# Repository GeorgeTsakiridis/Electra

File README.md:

Electra is a WIP DRSSTC Tesla Coil, aimed to have a power rating of about 7-8 kW.

<h1>Project Structure:</h1>
<ul>
   <li>DRSSTC MIDI Interrupter: The original Interrupter Controller.</li>
   <li>DRSSTC MIDI Interrupter 2: The new Interrupter Controller.</li>
   <li>Model: A 3D Model of the Tesla Coil.</li>
</ul>

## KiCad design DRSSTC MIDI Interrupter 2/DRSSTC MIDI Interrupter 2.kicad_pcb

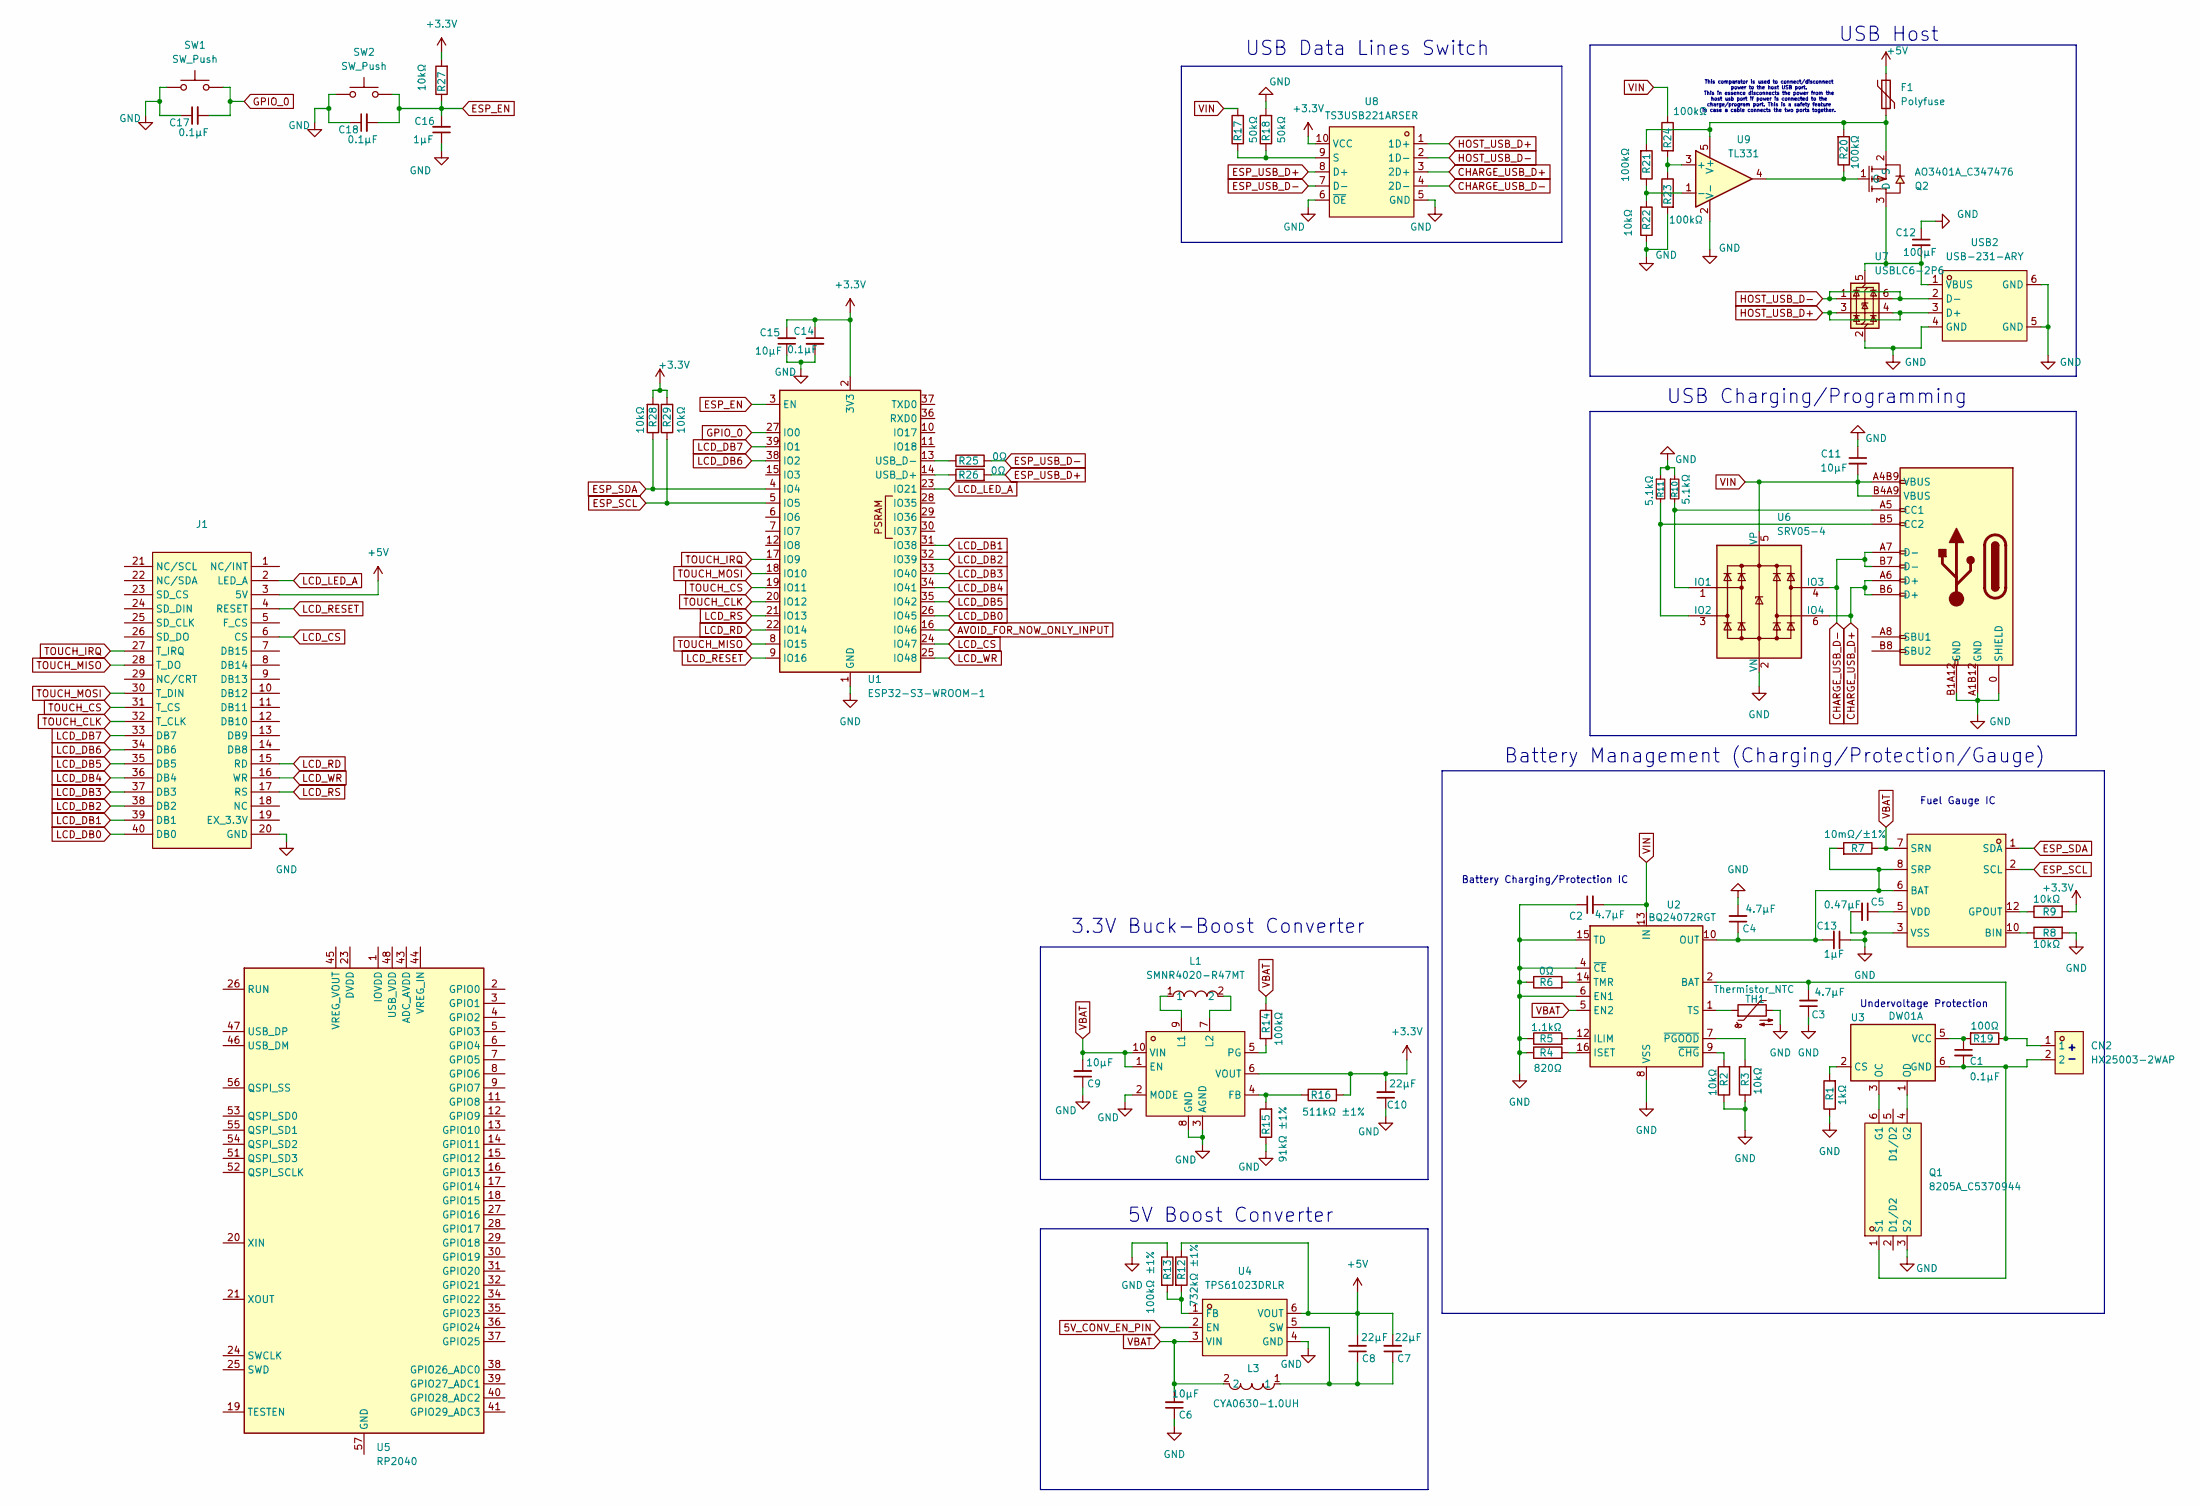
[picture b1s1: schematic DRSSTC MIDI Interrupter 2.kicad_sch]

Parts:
C1, C14, C17, C18: 0.1μF; C_0805_2012Metric_Pad1.18x1.45mm_HandSolder
C2, C3, C4: 4.7μF; C_0805_2012Metric_Pad1.18x1.45mm_HandSolder
C5: 0.47μF; C_0805_2012Metric_Pad1.18x1.45mm_HandSolder
C6, C9, C11, C15: 10μF; C_0805_2012Metric_Pad1.18x1.45mm_HandSolder
C7, C8, C10: 22μF; C_0805_2012Metric_Pad1.18x1.45mm_HandSolder
C12: 100μF; C_0805_2012Metric_Pad1.18x1.45mm_HandSolder
C13, C16: 1μF; C_0805_2012Metric_Pad1.18x1.45mm_HandSolder
CN2: HX25003-2WAP; CONN-TH_2P-P2.50_HX25003-2WAP; LCSC Part C442326
F1: Polyfuse; R_0805_2012Metric_Pad1.20x1.40mm_HandSolder; LCSC ID C2843994
J1: LCD
L1: SMNR4020-R47MT; IND-SMD_L4.0-W4.0_SMNR4020; LCSC Part C467058
L3: CYA0630-1.0UH; IND-SMD_L7.2-W6.6_GPSR0730; LCSC Part C5189744
Q1: 8205A_C5370944; SOT-23-6_L2.9-W1.6-P0.95-LS2.8-BR; LCSC Part C5370944
Q2: AO3401A_C347476; SOT-23_L2.9-W1.3-P1.90-LS2.4-BR; LCSC Part C347476
R1: 1kΩ; R_0805_2012Metric_Pad1.20x1.40mm_HandSolder
R2, R3, R8, R9, R22, R27, R28, R29: 10kΩ; R_0805_2012Metric_Pad1.20x1.40mm_HandSolder
R4: 820Ω; R_0805_2012Metric_Pad1.20x1.40mm_HandSolder
R5: 1.1kΩ; R_0805_2012Metric_Pad1.20x1.40mm_HandSolder
R6, R25, R26: 0Ω; R_0805_2012Metric_Pad1.20x1.40mm_HandSolder
R7: 10mΩ/±1%; R_1206_3216Metric_Pad1.30x1.75mm_HandSolder
R10, R11: 5.1kΩ; R_0805_2012Metric
R12: 732kΩ ±1%; R_0805_2012Metric_Pad1.20x1.40mm_HandSolder
R13: 100kΩ ±1%; R_0805_2012Metric_Pad1.20x1.40mm_HandSolder
R14, R20, R21, R23, R24: 100kΩ; R_0805_2012Metric_Pad1.20x1.40mm_HandSolder
R15: 91kΩ ±1%; R_0805_2012Metric_Pad1.20x1.40mm_HandSolder
R16: 511kΩ ±1%; R_0805_2012Metric_Pad1.20x1.40mm_HandSolder
R17, R18: 50kΩ; R_0805_2012Metric_Pad1.20x1.40mm_HandSolder
R19: 100Ω; R_0805_2012Metric_Pad1.20x1.40mm_HandSolder
SW1, SW2: SW_Push
TH1: Thermistor_NTC
U1: ESP32-S3-WROOM-1
U2: BQ24072RGT; VQFN-16-1EP_3x3mm_P0.5mm_EP1.6x1.6mm
U3: DW01A; SOT-23-6
U4: TPS61023DRLR; SOT-563_L1.6-W1.2-P0.50-LS1.6-BR; LCSC Part C919459
U5: RP2040; QFN-56-1EP_7x7mm_P0.4mm_EP3.2x3.2mm
U6: SRV05-4; SOT-23-6_L2.9-W1.6-P0.95-LS2.8-BR
U7: USBLC6-2P6; SOT-666
U8: TS3USB221ARSER; UQFN-10_L2.0-W1.5-P0.50-BL; LCSC Part C128396
U9: TL331; SOT-23-5; LCSC Part Number C80942
U10: TPS63802DLAR; VSON-10_L3.0-W2.0-P0.50-TL; LCSC Part C2845237
U11: BQ27441DRZR-G1B; SON-12_L4.0-W2.5-P0.40-BL-EP; LCSC Part C473374
USB1: HH 16P-CB TYPE-C (Y007); USB-C-SMD_HH-16P-CB-TYPE-C-Y007; LCSC Part C52711231
USB2: USB-231-ARY; USB-A-TH_USB-231-ARY; LCSC Part C720525

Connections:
5V_CONV_EN_PIN: U4.2 (EN)
+3.3V: C10.2, C14.1, C15.2, R9.2, R16.2, R27.2, R28.2, R29.2, U1.2 (3V3), U8.10 (VCC), U10.6 (VOUT)
+5V: C7.2, C8.2, F1.1, J1.3 (5V), R12.1, U4.6 (VOUT)
AVOID_FOR_NOW_ONLY_INPUT: U1.16 (IO46)
CHARGE_USB_D+: U6.6 (IO4), U8.3 (2D+), USB1.A6 (D+), USB1.B6 (D+)
CHARGE_USB_D-: U6.4 (IO3), U8.4 (2D-), USB1.A7 (D-), USB1.B7 (D-)
ESP_EN: C16.2, C18.2, R27.1, SW2.2, U1.3 (EN)
ESP_SCL: R29.1, U1.5 (IO5), U11.2 (SCL)
ESP_SDA: R28.1, U1.4 (IO4), U11.1 (SDA)
ESP_USB_D+: R26.2, U8.8 (D+)
ESP_USB_D-: R25.2, U8.7 (D-)
GND: C2.1, C3.1, C4.2, C5.2, C6.1, C9.1, C10.1, C11.1, C12.1, C13.1, C14.2, C15.1, C16.1, C17.1, C18.1, J1.20 (GND), Q1.3 (S2), R1.1, R2.1, R3.1, R4.1, R5.1, R6.1, R8.2, R10.1, R11.1, R13.1, R15.1, R18.2, R22.1, R23.2, SW1.1, SW2.1, TH1.2, U1.1 (GND), U1.40 (GND), U1.41 (GND), U2.4 (~CE), U2.6 (EN1), U2.8 (VSS), U2.15 (TD), U2.17 (VSS), U4.4 (GND), U6.2 (VN), U7.2 (GND), U8.5 (GND), U8.6 (~OE), U9.2 (V-), U10.2 (MODE), U10.3 (AGND), U10.8 (GND), U11.3 (VSS), USB1.0 (SHIELD), USB1.A1B12 (GND), USB1.B1A12 (GND), USB2.4 (GND), USB2.5 (GND), USB2.6 (GND)
GPIO_0: C17.2, SW1.2, U1.27 (IO0)
HOST_USB_D+: U7.3 (I/O2), U7.4 (I/O2), U8.1 (1D+), USB2.3 (D+)
HOST_USB_D-: U7.1 (I/O1), U7.6 (I/O1), U8.2 (1D-), USB2.2 (D-)
LCD_CS: J1.6 (CS), U1.24 (IO47)
LCD_DB0: J1.40 (DB0), U1.26 (IO45)
LCD_DB1: J1.39 (DB1), U1.31 (IO38)
LCD_DB2: J1.38 (DB2), U1.32 (IO39)
LCD_DB3: J1.37 (DB3), U1.33 (IO40)
LCD_DB4: J1.36 (DB4), U1.34 (IO41)
LCD_DB5: J1.35 (DB5), U1.35 (IO42)
LCD_DB6: J1.34 (DB6), U1.38 (IO2)
LCD_DB7: J1.33 (DB7), U1.39 (IO1)
LCD_LED_A: J1.2 (LED_A), U1.23 (IO21)
LCD_RD: J1.15 (RD), U1.22 (IO14)
LCD_RESET: J1.4 (RESET), U1.9 (IO16)
LCD_RS: J1.17 (RS), U1.21 (IO13)
LCD_WR: J1.16 (WR), U1.25 (IO48)
unnamed: C3.2, CN2.1, R19.1, U2.2 (BAT), U2.3 (BAT)
unnamed: Q1.6 (G1), U3.3 (OC)
unnamed: Q1.4 (G2), U3.1 (OD)
unnamed: C1.2, CN2.2, Q1.1 (S1), U3.6 (GND)
unnamed: C12.2, Q2.3 (D), U7.5 (VBUS), USB2.1 (VBUS)
unnamed: Q2.1 (G), R20.1, U9.4
unnamed: F1.2, Q2.2 (S), R20.2, R21.2, U9.5 (V+)
unnamed: R26.1, U1.14 (USB_D+)
unnamed: R25.1, U1.13 (USB_D-)
unnamed: R5.2, U2.12 (ILIM)
unnamed: R4.2, U2.16 (ISET)
unnamed: R6.2, U2.14 (TMR)
unnamed: TH1.1, U2.1 (TS)
unnamed: R2.2, U2.9 (~CHG)
unnamed: R3.2, U2.7 (~PGOOD)
unnamed: R1.2, U3.2 (CS)
unnamed: C1.1, R19.2, U3.5 (VCC)
unnamed: R12.2, R13.2, U4.1 (FB)
unnamed: C7.1, C8.1, L3.1, U4.5 (SW)
unnamed: U5.23 (DVDD), U5.50 (DVDD)
unnamed: U5.1 (IOVDD), U5.10 (IOVDD), U5.22 (IOVDD), U5.33 (IOVDD), U5.42 (IOVDD), U5.49 (IOVDD)
unnamed: R10.2, U6.1 (IO1), USB1.A5 (CC1)
unnamed: R11.2, U6.3 (IO2), USB1.B5 (CC2)
unnamed: R17.1, R18.1, U8.9 (S)
unnamed: R23.1, R24.2, U9.3 (+)
unnamed: R21.1, R22.2, U9.1 (-)
unnamed: R15.2, R16.1, U10.4 (FB)
unnamed: L1.1, U10.9 (L1)
unnamed: L1.2, U10.7 (L2)
unnamed: R14.2, U10.5 (PG)
unnamed: C4.1, C13.2, R7.2, U2.10 (OUT), U2.11 (OUT), U11.6 (BAT), U11.8 (SRP)
unnamed: R8.1, U11.10 (BIN)
unnamed: R9.1, U11.12 (GPOUT)
unnamed: C5.1, U11.5 (VDD)
TOUCH_CLK: J1.32 (T_CLK), U1.20 (IO12)
TOUCH_CS: J1.31 (T_CS), U1.19 (IO11)
TOUCH_IRQ: J1.27 (T_IRQ), U1.17 (IO9)
TOUCH_MISO: J1.28 (T_DO), U1.8 (IO15)
TOUCH_MOSI: J1.30 (T_DIN), U1.18 (IO10)
VBAT: C6.2, C9.2, L3.2, R7.1, R14.1, U2.5 (EN2), U4.3 (VIN), U10.1 (EN), U10.10 (VIN), U11.7 (SRN)
VIN: C2.2, C11.2, R17.2, R24.1, U2.13 (IN), U6.5 (VP), USB1.A4B9 (VBUS), USB1.B4A9 (VBUS)

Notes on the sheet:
Battery Management (Charging/Protection/Gauge)
+ -
5V Boost Converter
This comparator is used to connect/disconnect power to the host USB port. This in essence disconnects the power from the host usb port if power is connected to the charge/program port. This is a safety feature in case a cable connects the two ports together.
3.3V Buck-Boost Converter
Fuel Gauge IC
USB Data Lines Switch
USB Host
USB Charging/Programming
Battery Charging/Protection IC
Undervoltage Protection

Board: 2 copper layers, 67 parts (0 on the bottom side), 67 nets, no tracks yet.

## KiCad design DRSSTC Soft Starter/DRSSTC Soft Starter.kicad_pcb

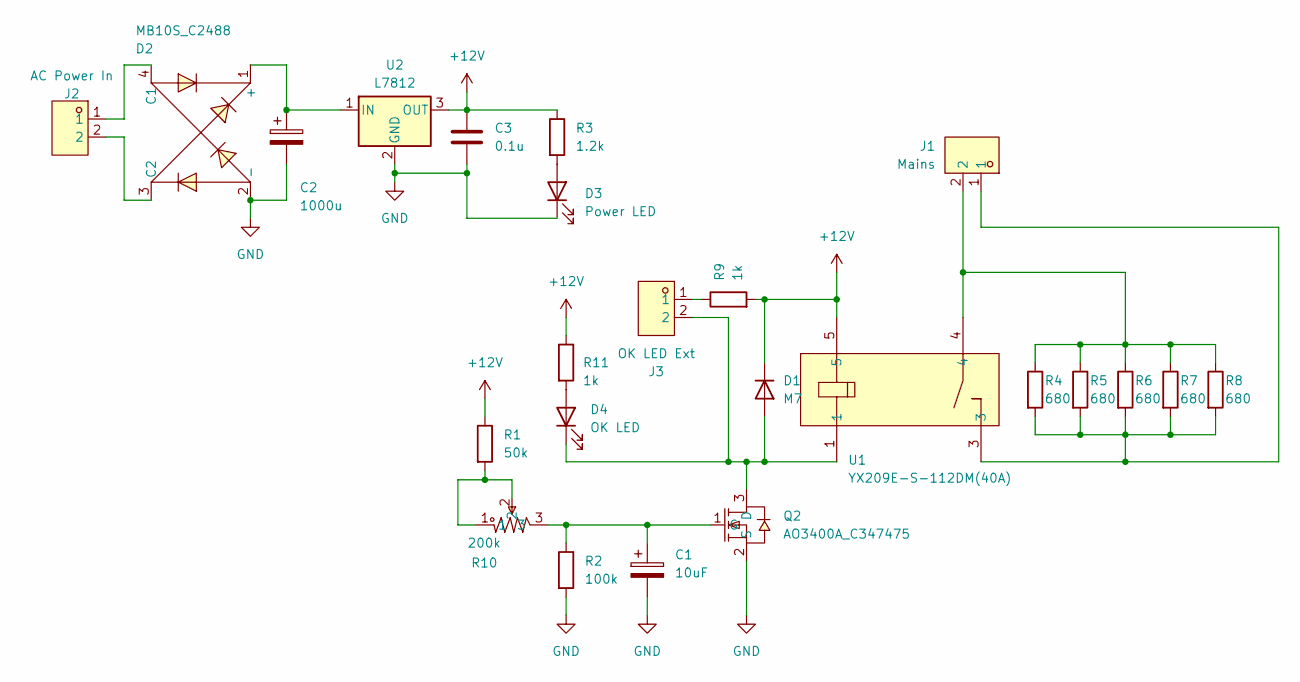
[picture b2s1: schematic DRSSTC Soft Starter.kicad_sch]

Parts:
C1: 10uF; C_0805_2012Metric_Pad1.18x1.45mm_HandSolder
C2: 1000u; CAP-TH_BD10.0-P5.00-D1.0-FD
C3: 0.1u; C_0805_2012Metric_Pad1.18x1.45mm_HandSolder
D1: M7; D_SMA_Handsoldering
D2: MB10S_C2488; MBS_L4.7-W3.8-P2.40-LS7.0-TL; LCSC Part C2488
D3: Power LED; LED_0805_2012Metric_Pad1.15x1.40mm_HandSolder
D4: OK LED; LED_0805_2012Metric_Pad1.15x1.40mm_HandSolder
J1: Mains; CONN-TH_P6.35_KF635-6.35-2P; LCSC Part C475102
J2: AC Power In; CONN-TH_XH-2A; LCSC Part C5258883
J3: OK LED Ext; CONN-TH_XH-2A; LCSC Part C5258883
Q2: AO3400A_C347475; SOT-23-3_L2.9-W1.3-P1.90-LS2.4-BR; LCSC Part C347475
R1: 50k; R_0805_2012Metric
R2: 100k; R_0805_2012Metric
R3: 1.2k; R_0805_2012Metric
R4, R5, R6, R7, R8: 680; R_Axial_Power_L48.0mm_W12.5mm_P55.88mm
R9, R11: 1k; R_0805_2012Metric
R10: 200k; RES-ADJ-TH_3P-L10.0-W10.0-P2.50-L; LCSC Part C118954
U1: YX209E-S-112DM(40A); RELAY-TH_YX209E-S-112DM; LCSC Part C19193906
U2: L7812; TO-252-2

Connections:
+12V: C3.1, D1.1 (K), R1.1, R3.1, R9.2, R11.1, U1.5, U2.3 (OUT)
GND: C1.2, C2.2, C3.2, D2.2 (-), D3.1 (K), Q2.2 (S), R2.2, U2.2 (GND)
unnamed: D1.2 (A), D4.1 (K), J3.2, Q2.3 (D), U1.1
unnamed: C2.1, D2.1 (+), U2.1 (IN)
unnamed: D2.4 (C1), J2.1
unnamed: D2.3 (C2), J2.2
unnamed: D3.2 (A), R3.2
unnamed: D4.2 (A), R11.2
unnamed: J1.1, R4.2, R5.2, R6.2, R7.2, R8.2, U1.3
unnamed: J1.2, R4.1, R5.1, R6.1, R7.1, R8.1, U1.4
unnamed: J3.1, R9.1
unnamed: C1.1, Q2.1 (G), R2.1, R10.3
unnamed: R1.2, R10.1, R10.2

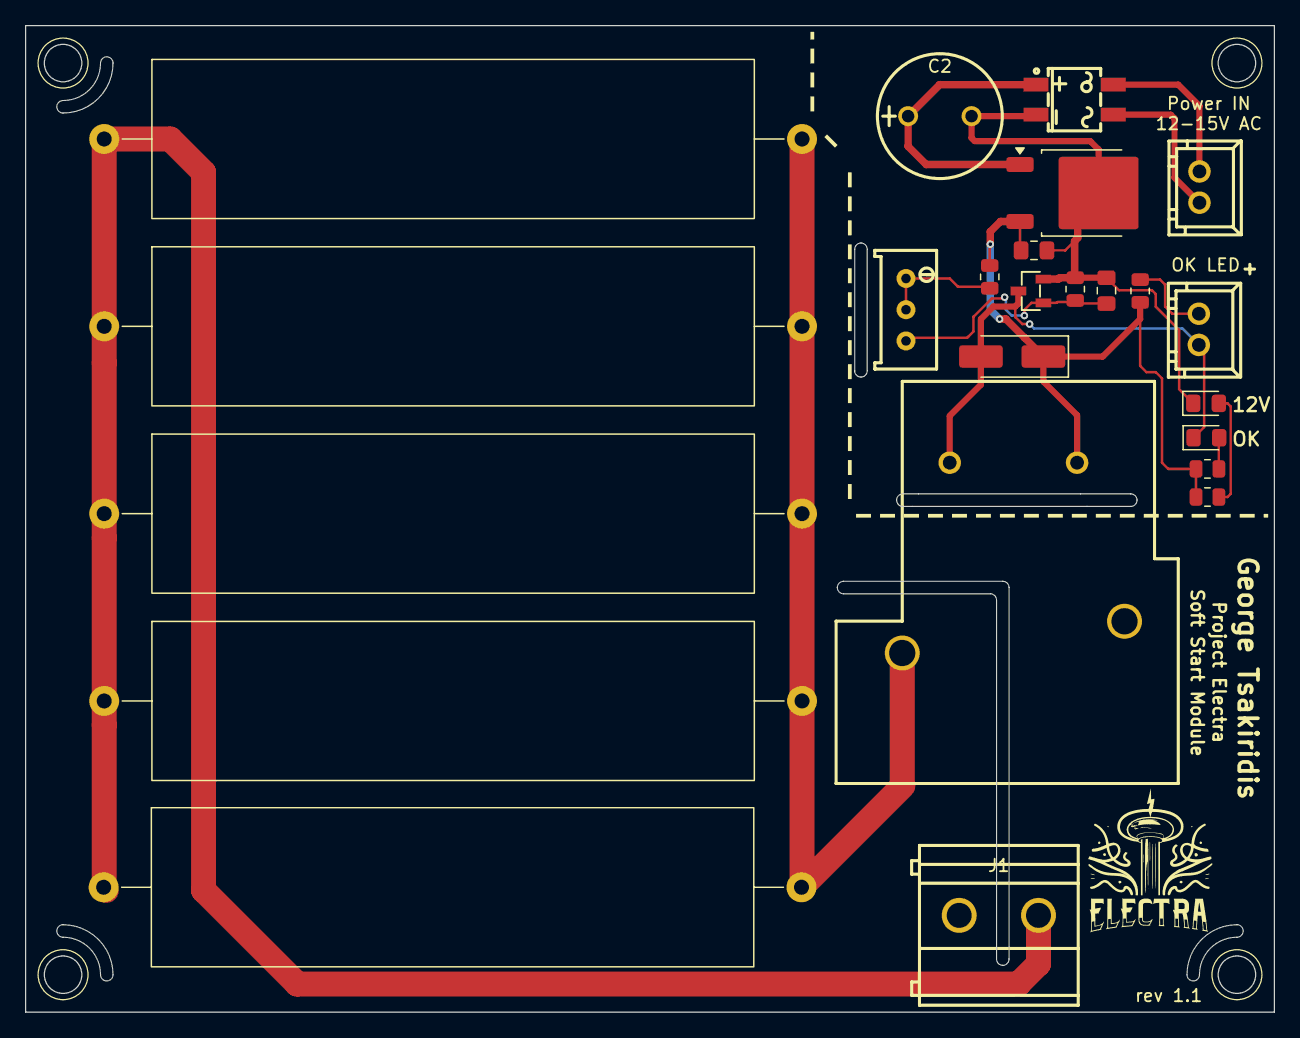
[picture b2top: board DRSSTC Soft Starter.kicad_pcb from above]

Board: 2 copper layers, 100.0 x 79.0 mm, 24 parts (0 on the bottom side), 13 nets.

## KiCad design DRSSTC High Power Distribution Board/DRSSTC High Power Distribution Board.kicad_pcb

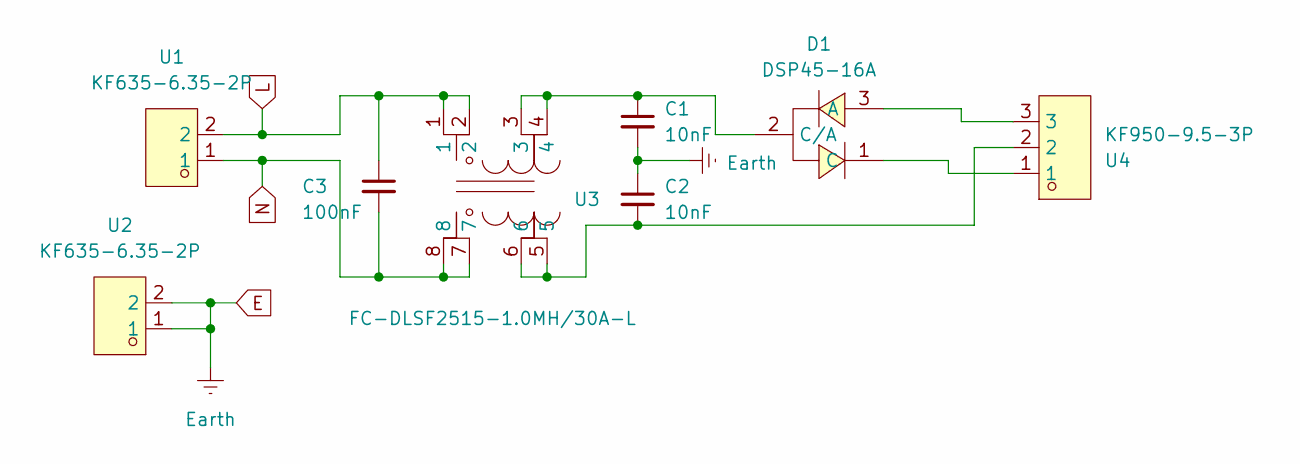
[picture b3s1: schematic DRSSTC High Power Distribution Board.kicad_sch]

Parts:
C1, C2: 10nF; CAP-TH_L13.0-W6.0-P10.00-D0.6
C3: 100nF; CAP-TH_L26.5-W11.0-P22.50-D1.4
D1: DSP45-16A; TO-247-3_L15.9-W5.1-P5.44-L; LCSC Part C426676
U1, U2: KF635-6.35-2P; CONN-TH_P6.35_KF635-6.35-2P; LCSC Part C475102
U3: FC-DLSF2515-1.0MH/30A-L; FILTER-TH_8P-L25.0-W18.0; LCSC Part C18164943
U4: KF950-9.5-3P; CONN-TH_3P-P9.50_KF950-9.5-3P; LCSC Part C475107

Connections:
E: C1.2, C2.1, U2.1, U2.2
L: C3.1, U1.2, U3.1, U3.2
N: C3.2, U1.1, U3.7, U3.8
unnamed: C2.2, U3.5, U3.6, U4.2
unnamed: D1.3 (A), U4.3
unnamed: D1.1 (C), U4.1
unnamed: C1.1, D1.2 (C/A), U3.3, U3.4

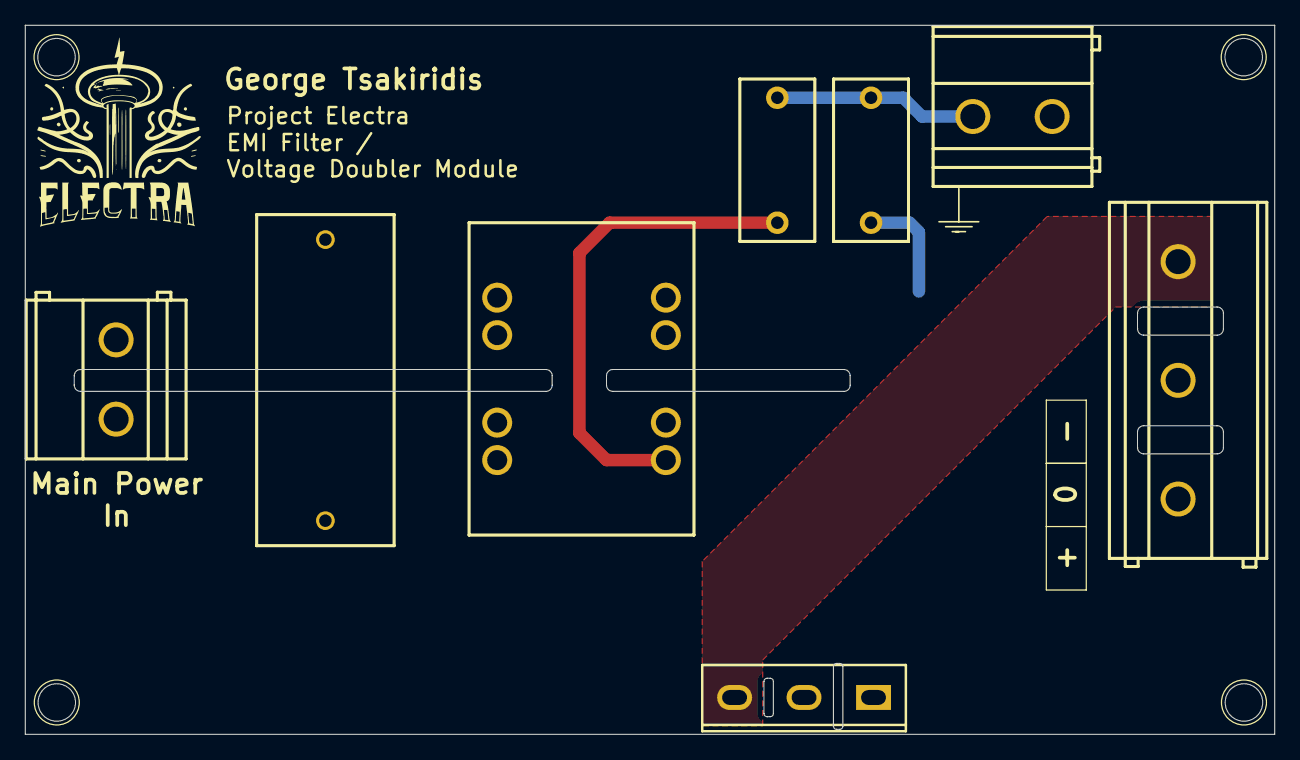
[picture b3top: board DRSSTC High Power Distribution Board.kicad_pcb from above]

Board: 2 copper layers, 100.0 x 56.8 mm, 8 parts (0 on the bottom side), 7 nets.

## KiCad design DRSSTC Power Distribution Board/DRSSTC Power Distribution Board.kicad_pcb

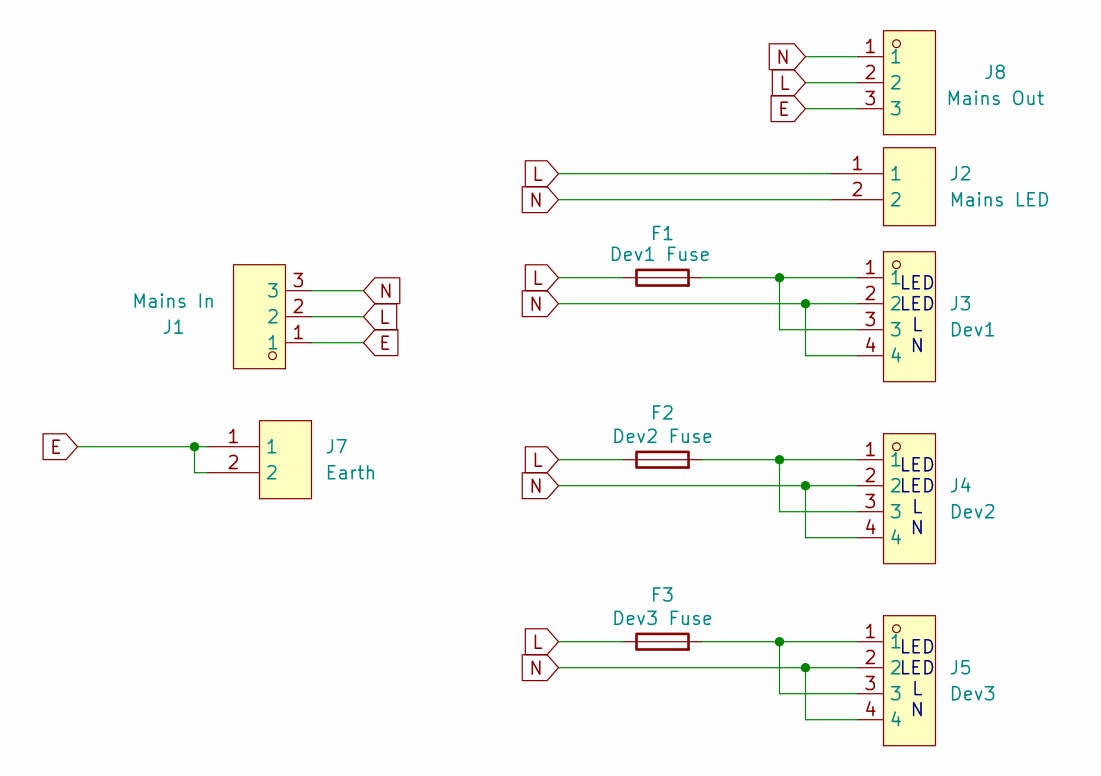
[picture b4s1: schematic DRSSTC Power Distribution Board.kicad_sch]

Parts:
F1: Dev1 Fuse; FUSE-TH_L24.8-W9.8-P22.60
F2: Dev2 Fuse; FUSE-TH_L24.8-W9.8-P22.60
F3: Dev3 Fuse; FUSE-TH_L24.8-W9.8-P22.60
J1: Mains In; CONN-TH_3P-P6.35_KF635-6.35-3P; LCSC Part C475103
J2: Mains LED; CONN-TH_2P-P5.00_WJ500V-5.08-2P; LCSC Part C8465
J3: Dev1; CONN-TH_4P_DB128L-5.08-4P-GN-S; LCSC Part C2827883
J4: Dev2; CONN-TH_4P_DB128L-5.08-4P-GN-S; LCSC Part C2827883
J5: Dev3; CONN-TH_4P_DB128L-5.08-4P-GN-S; LCSC Part C2827883
J7: Earth; CONN-TH_2P-P5.00_WJ500V-5.08-2P; LCSC Part C8465
J8: Mains Out; CONN-TH_3P-P6.35_KF635-6.35-3P; LCSC Part C475103

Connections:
E: J1.1, J7.1, J7.2, J8.3
L: F1.1, F2.1, F3.1, J1.2, J2.1, J8.2
N: J1.3, J2.2, J3.2, J3.4, J4.2, J4.4, J5.2, J5.4, J8.1
unnamed: F1.2, J3.1, J3.3
unnamed: F2.2, J4.1, J4.3
unnamed: F3.2, J5.1, J5.3

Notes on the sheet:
LED LED L N

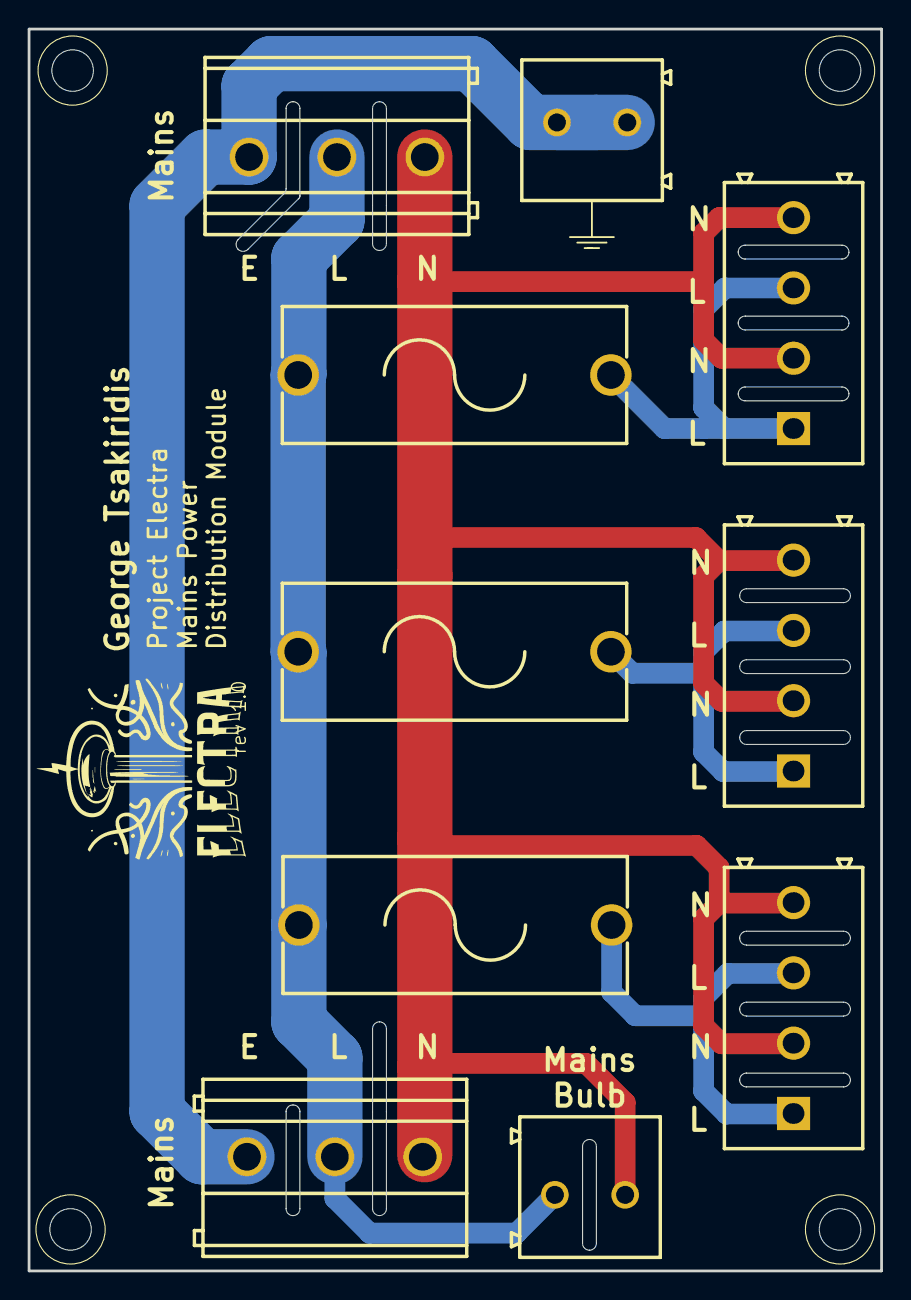
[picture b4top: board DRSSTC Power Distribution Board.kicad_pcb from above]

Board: 2 copper layers, 61.6 x 89.8 mm, 10 parts (0 on the bottom side), 6 nets.

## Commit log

2025-12-04 Initial High Power Distribution Board commit
2025-12-04 Initial commit of components
